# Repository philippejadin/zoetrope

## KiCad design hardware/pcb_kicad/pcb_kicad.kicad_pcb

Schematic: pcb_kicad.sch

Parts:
C1: 100uF; CP_Radial_D6.3mm_P2.50mm
D1: 1N4004; D_DO-41_SOD81_P10.16mm_Horizontal
Driver1: Pololu_Breakout_A4988; Pololu_Breakout-16_15.2x20.3mm
H2, H3, H4: MountingHole; MountingHole_3.2mm_M3
J1, J2, J3, J4, J5: Screw_Terminal_01x02; TerminalBlock_bornier-2_P5.08mm
J6: Conn_02x05_Counter_Clockwise; IDC-Header_2x05_P2.54mm_Vertical
Nano1: Arduino_Nano_v3.x; Arduino_Nano
Q1, Q2: IRLB8721PBF; TO-220-3_Vertical
R1, R3: 220; R_Axial_DIN0309_L9.0mm_D3.2mm_P2.54mm_Vertical
R2, R4, R5: 100K; R_Axial_DIN0309_L9.0mm_D3.2mm_P2.54mm_Vertical
RV1, RV2, RV3: R_POT; Potentiometer_Alps_RK163_Single_Horizontal
U1: LM7805_TO220; TO-220-3_Vertical

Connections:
+5V: Driver1.2 (VDD), J6.1, Nano1.27 (+5V), R5.1, RV1.1, RV2.1, RV3.1, U1.3 (VO)
+12V: C1.1, D1.1 (K), Driver1.8 (VMOT), J4.2, J5.2, U1.1 (VI)
/D2: J6.3, Nano1.5 (D2)
/D3: J6.5, Nano1.6 (D3)
/D7: J6.7, Nano1.10 (D7)
/D8: J6.9, Nano1.11 (D8)
/DIR: Driver1.16 (DIR), Nano1.9 (D6)
/ENABLE: Driver1.9 (~ENABLE), Nano1.7 (D4), R5.2
/LED1: Nano1.12 (D9), R1.2
/LED2: Nano1.13 (D10), R3.2
/MS1: Driver1.10 (MS1), Nano1.14 (D11)
/MS2: Driver1.11 (MS2), Nano1.15 (D12)
/MS3: Driver1.12 (MS3), Nano1.16 (D13)
/STEP: Driver1.15 (STEP), Nano1.8 (D5)
GND: C1.2, Driver1.1 (GND), Driver1.7 (GND), J1.1, J6.2, Nano1.4 (GND), Nano1.29 (GND), Q1.3 (S), Q2.3 (S), R2.2, R4.2, RV1.3, RV2.3, RV3.3, U1.2 (GND)
unnamed: D1.2 (A), J1.2
unnamed: Driver1.3 (1B), J2.2
unnamed: Driver1.4 (1A), J2.1
unnamed: Driver1.5 (2A), J3.2
unnamed: Driver1.6 (2B), J3.1
unnamed: Driver1.13 (~RESET), Driver1.14 (~SLEEP)
unnamed: J4.1, Q1.2 (D)
unnamed: J5.1, Q2.2 (D)
unnamed: Nano1.19 (A0), RV1.2
unnamed: Nano1.20 (A1), RV2.2
unnamed: Nano1.21 (A2), RV3.2
unnamed: Q1.1 (G), R1.1, R2.1
unnamed: Q2.1 (G), R3.1, R4.1

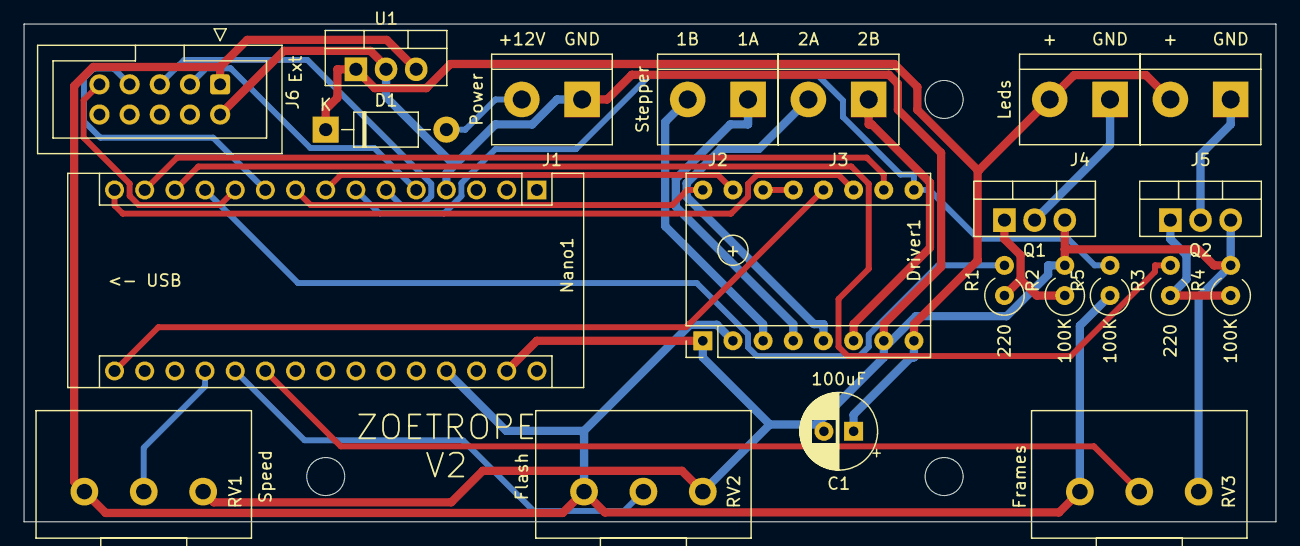
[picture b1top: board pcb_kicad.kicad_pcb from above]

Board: 2 copper layers, 105.4 x 41.9 mm, 24 parts (0 on the bottom side), 28 nets.

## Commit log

2021-09-28 initail commit
2021-09-29 nouvelle version
2021-10-01 nouvelles versions
2021-10-02 using kicad
2021-10-03 better latyout?
2021-10-04 rework
2021-10-08 best run so far
2021-10-15 methode millis fonctionne !
2021-10-15 better
2021-10-15 using smoothed. New approach!
2021-10-15 remove intermitent flicker when changing speed
2021-10-18 v1 pour pcb v1
2021-10-22 minor changes / debug stuff
2021-10-22 allow set frames per disk using third pot
2021-10-22 max acceleration control of stepper
2021-10-22 better flash control
2021-10-22 accell
2021-10-22 new pcb
2021-10-22 v2 to be checked
2021-10-24 final revision of PCB V1
2021-10-24 v1.1
2021-10-24 v 1.1 to be checked
2021-10-28 built in led flash
2021-10-28 pcb V2 wip
2021-10-28 latest V
2021-10-30 added enclosure, removed old fritzing files
2021-10-30 moved pcb files
